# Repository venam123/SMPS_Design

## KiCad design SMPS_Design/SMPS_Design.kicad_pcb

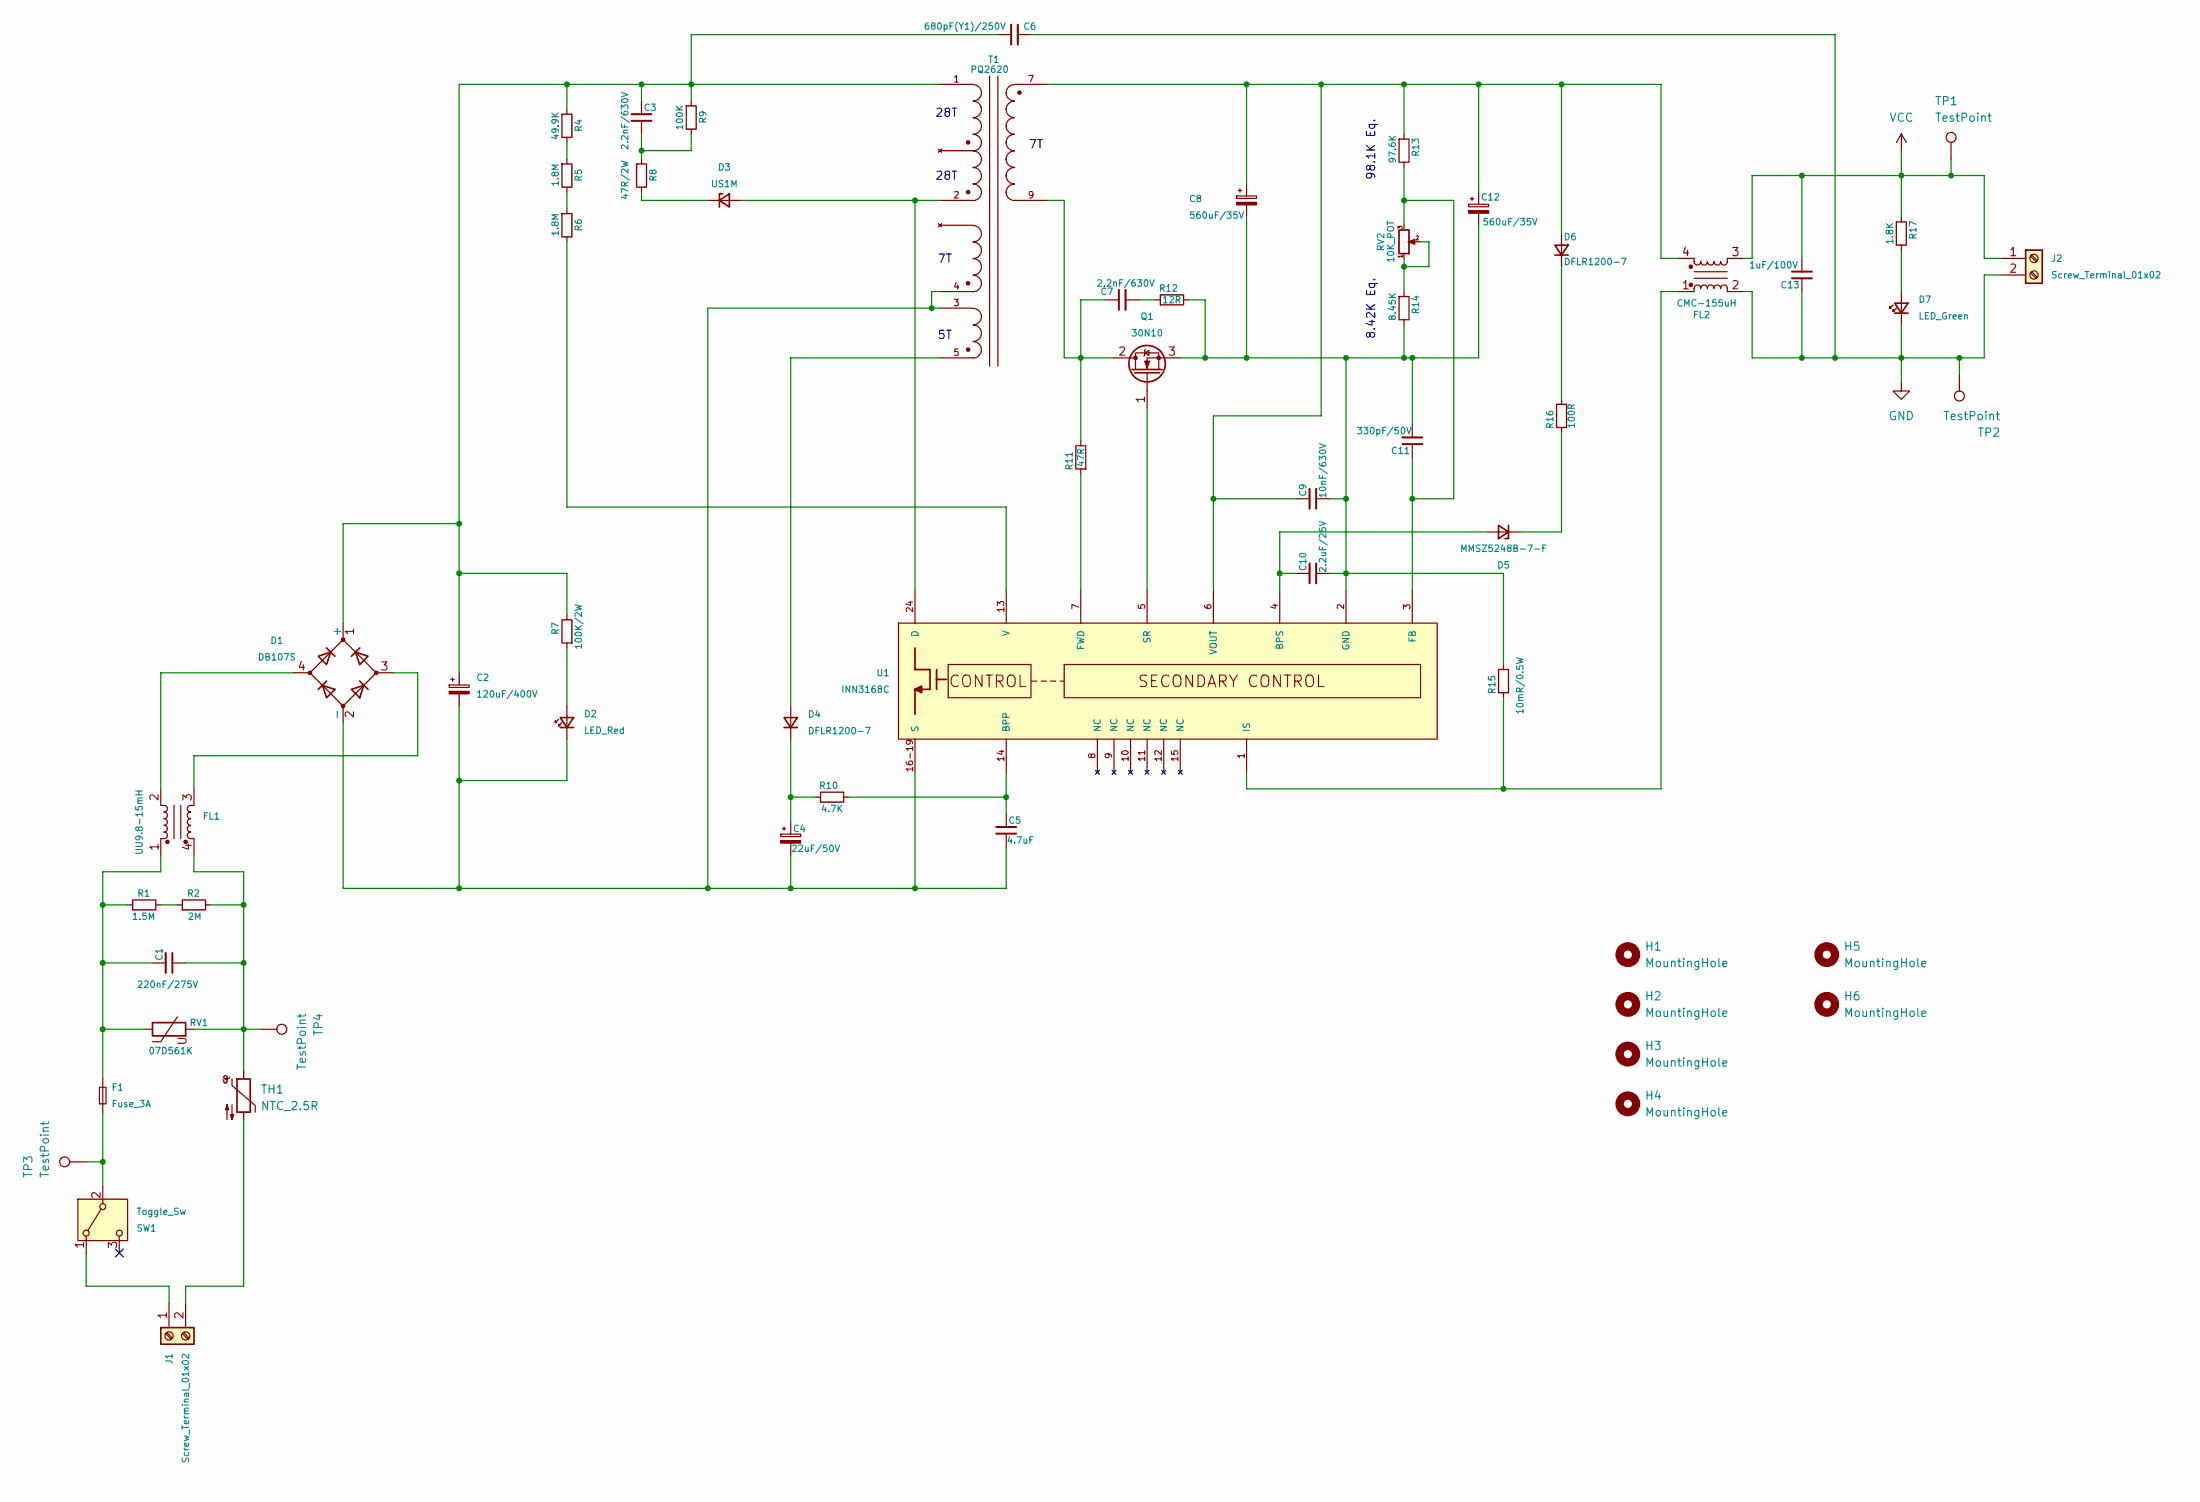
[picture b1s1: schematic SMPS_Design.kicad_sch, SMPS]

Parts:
C1: 220nF/275V; C_Rect_L13.0mm_W6.0mm_P10.00mm_FKS3_FKP3_MKS4
C2: 120uF/400V; CP_Radial_D18.0mm_P7.50mm
C3, C7: 2.2nF/630V; C_1206_3216Metric_Pad1.33x1.80mm_HandSolder
C4: 22uF/50V; CP_Radial_D5.0mm_P2.00mm
C5: 4.7uF; C_0805_2012Metric_Pad1.18x1.45mm_HandSolder
C6: 680pF(Y1)/250V; C_Disc_D9.0mm_W5.0mm_P10.00mm
C8, C12: 560uF/35V; CP_Radial_D10.0mm_P5.00mm
C9: 10nF/630V; C_1206_3216Metric_Pad1.33x1.80mm_HandSolder
C10: 2.2uF/25V; C_0805_2012Metric_Pad1.18x1.45mm_HandSolder
C11: 330pF/50V; C_0603_1608Metric_Pad1.08x0.95mm_HandSolder
C13: 1uF/100V; C_0805_2012Metric_Pad1.18x1.45mm_HandSolder
D1: DB107S; Diode_Bridge_Diotec_SO-DIL-Slim
D2: LED_Red; LED_D3.0mm
D3: US1M; D_SMA
D4, D6: DFLR1200-7; D_PowerDI-123
D5: MMSZ5248B-7-F; D_SOD-123
D7: LED_Green; LED_D3.0mm_Clear
F1: Fuse_3A; Fuseholder_Cylinder-5x20mm_EATON_H15-V-1_Vertical_Closed; MFR Part# FH1-206Z
FL1: UU9.8-15mH
FL2: CMC-155uH; CommonMode_Chock
H1, H2, H3, H4: MountingHole; MountingHole_4.3mm_M4
H5, H6: MountingHole; MountingHole_2.2mm_M2
J1, J2: Screw_Terminal_01x02; TerminalBlock_Phoenix_MKDS-1,5-2-5.08_1x02_P5.08mm_Horizont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
Q1: 30N10; TO-252-3_TabPin2
R1: 1.5M; R_1206_3216Metric_Pad1.30x1.75mm_HandSolder
R2: 2M; R_1206_3216Metric_Pad1.30x1.75mm_HandSolder
R4: 49.9K; R_0805_2012Metric_Pad1.20x1.40mm_HandSolder
R5, R6: 1.8M; R_1206_3216Metric_Pad1.30x1.75mm_HandSolder
R7: 100K/2W; R_Axial_DIN0414_L11.9mm_D4.5mm_P5.08mm_Vertical
R8: 47R/2W; R_Axial_DIN0617_L17.0mm_D6.0mm_P5.08mm_Vertical
R9: 100K; R_1206_3216Metric_Pad1.30x1.75mm_HandSolder
R10: 4.7K; R_0603_1608Metric_Pad0.98x0.95mm_HandSolder
R11: 47R; R_0603_1608Metric_Pad0.98x0.95mm_HandSolder
R12: 12R; R_1206_3216Metric_Pad1.30x1.75mm_HandSolder
R13: 97.6K; R_0805_2012Metric_Pad1.20x1.40mm_HandSolder
R14: 8.45K; R_0805_2012Metric_Pad1.20x1.40mm_HandSolder
R15: 10mR/0.5W; R_0805_2012Metric_Pad1.20x1.40mm_HandSolder
R16: 100R; R_0603_1608Metric_Pad0.98x0.95mm_HandSolder
R17: 1.8K; R_0603_1608Metric_Pad0.98x0.95mm_HandSolder
RV1: 07D561K; RV_Disc_D7mm_W3.5mm_P5mm
RV2: 10K_POT; Potentiometer_Alpha_RD901F-40-00D_Single_Vertical_CircularH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
SW1: Toggle_Sw
T1: PQ2620
TH1: NTC_2.5R; RV_Disc_D12mm_W5mm_P7.5mm; MFR Part# MF112R505M4EP0CST0
TP1, TP2, TP3, TP4: TestPoint; TestPoint_Pad_D1.5mm
U1: INN3168C; INN3168C-H101-TL

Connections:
GND: C6.1, C13.1, D7.1 (K), FL2.2, J2.2, TP2.1 (1_1)
unnamed: C1.1, F1.2, FL1.1, R1.1, RV1.1
unnamed: C1.2, FL1.4, R2.2, RV1.2, TH1.1, TP4.1 (1_1)
unnamed: C3.2, R8.1, R9.2
unnamed: C7.2, R12.1
unnamed: C2.1, C3.1, C6.2, D1.1 (+), R4.1, R7.2, R9.1, T1.1
unnamed: C2.2, C4.2, C5.2, D1.2 (-), D2.1 (K), T1.3, T1.4, U1.16-19 (S)
unnamed: D1.3, FL1.3
unnamed: D1.4, FL1.2
unnamed: D2.2 (A), R7.1
unnamed: D3.2 (A), T1.2, U1.24 (D)
unnamed: D3.1 (K), R8.2
unnamed: D4.2 (A), T1.5
unnamed: C4.1, D4.1 (K), R10.1
unnamed: C10.1, D5.2 (A), U1.4 (BPS)
unnamed: D5.1 (K), R16.1
unnamed: C8.1, C9.1, C12.1, D6.2 (A), FL2.4, R13.1, T1.7, U1.6 (VOUT)
unnamed: D6.1 (K), R16.2
unnamed: D7.2 (A), R17.2
unnamed: J1.1, SW1.1 (A)
unnamed: J1.2, TH1.2
unnamed: C7.1, Q1.2 (D), R11.2, T1.9
unnamed: Q1.1 (G), U1.5 (SR)
unnamed: C8.2, C9.2, C10.2, C11.2, C12.2, Q1.3 (S), R12.2, R14.2, R15.2, U1.2 (GND)
unnamed: R1.2, R2.1
unnamed: R4.2, R5.1
unnamed: R5.2, R6.1
unnamed: R14.1, RV2.1, RV2.2
unnamed: F1.1, SW1.2 (B), TP3.1 (1_1)
unnamed: C5.1, R10.2, U1.14 (BPP)
unnamed: C11.1, R13.2, RV2.3, U1.3 (FB)
unnamed: R11.1, U1.7 (FWD)
unnamed: FL2.1, R15.1, U1.1 (IS)
unnamed: R6.2, U1.13 (V)
VCC: C13.2, FL2.3, J2.1, R17.1, TP1.1 (1_1)

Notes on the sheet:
28T
8.42K Eq.
98.1K Eq.

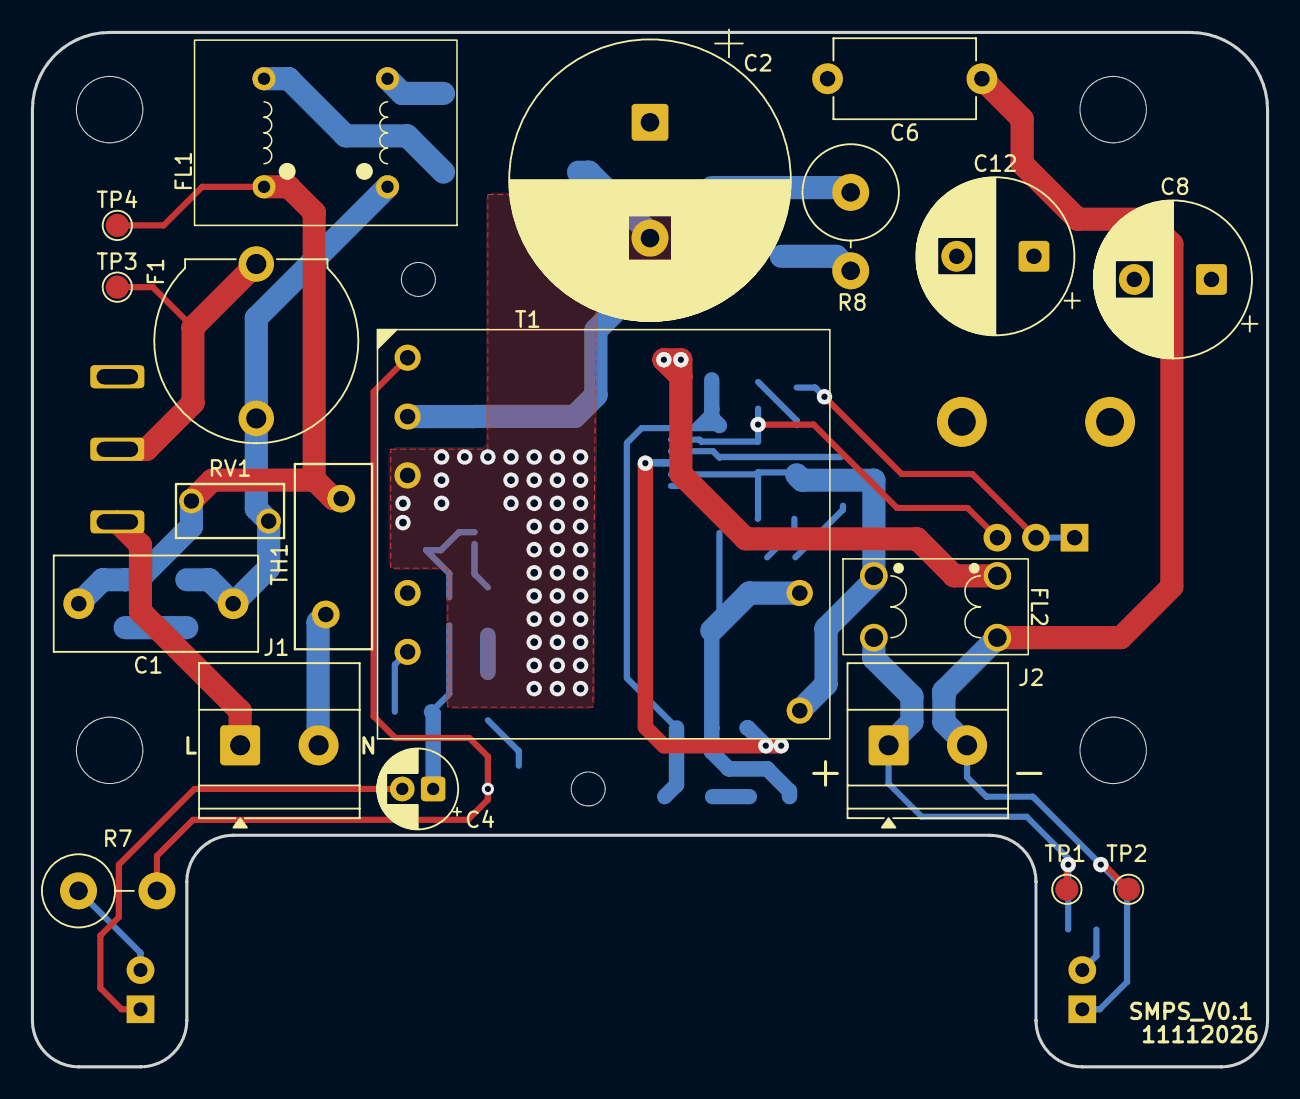
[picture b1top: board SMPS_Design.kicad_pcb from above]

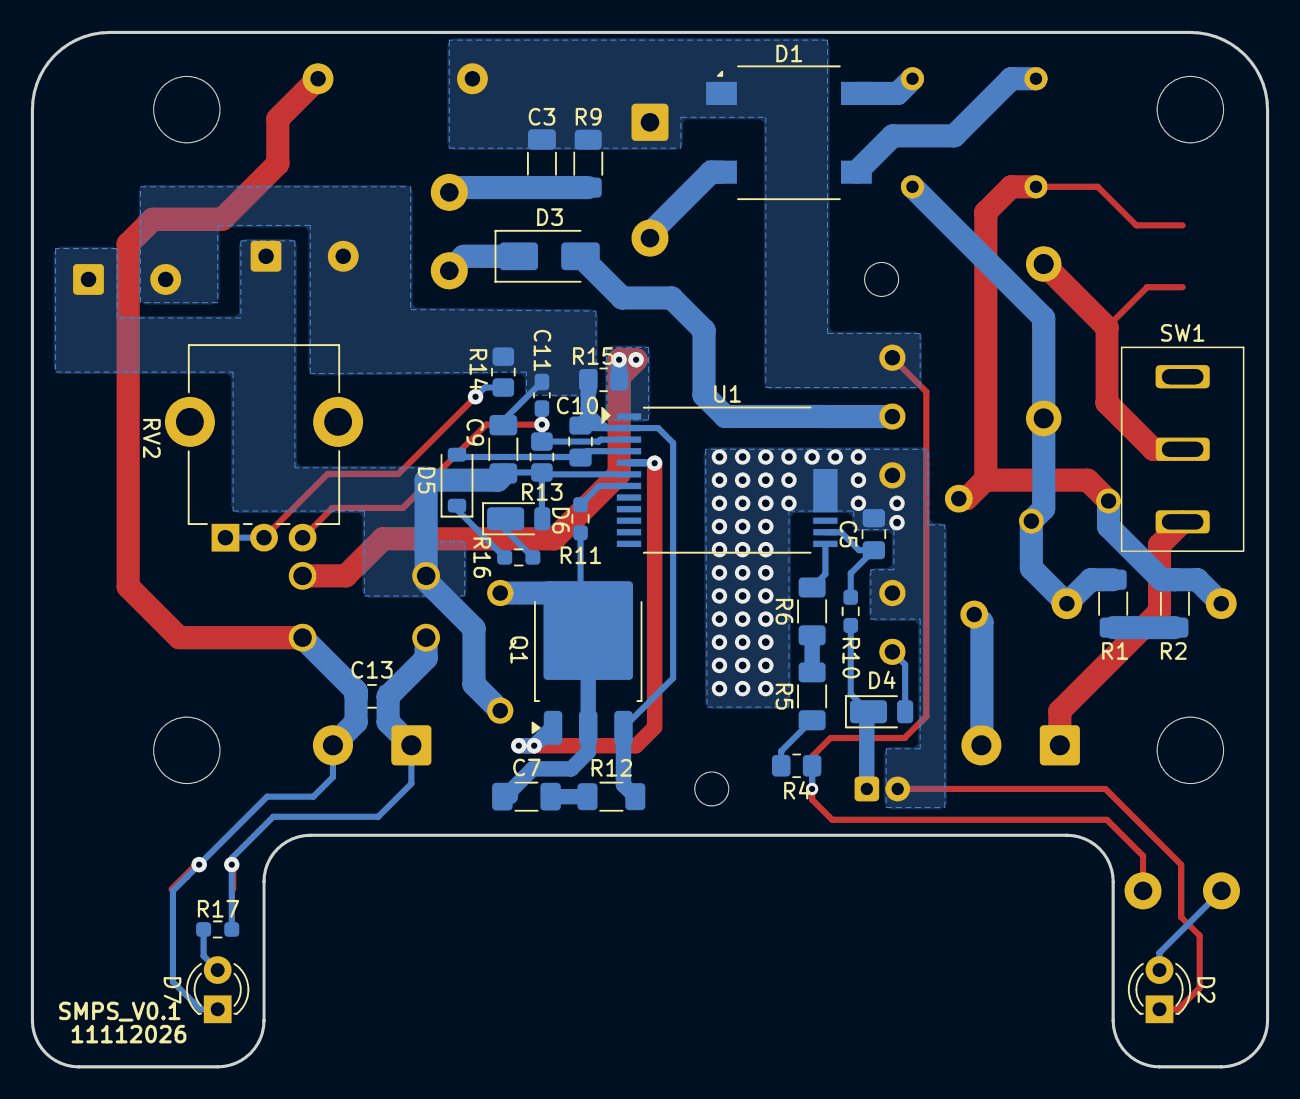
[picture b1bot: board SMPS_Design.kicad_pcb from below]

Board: 2 copper layers, 80.0 x 67.0 mm, 58 parts (32 on the bottom side), 35 nets.
